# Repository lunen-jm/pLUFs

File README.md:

# pLUFs

The Physical LUFS meter will be a project that allows users to have realtime analysis of the LUFs level of the audio being transmitted by their PC.

The datasheets for the projects are located in the `datasheets` folder. Note that information surrounding the circular display can be found here: 

* Getting started: https://wiki.seeedstudio.com/get_start_round_display/
* Hardware: https://wiki.seeedstudio.com/seeedstudio_round_display_usage/

Information regarding the stepper gauge can be found here:

* https://www.adafruit.com/product/2424 

Information regarding stepper motor driver can be found here:

* https://www.adafruit.com/product/2448 
* https://learn.adafruit.com/adafruit-tb6612-h-bridge-dc-stepper-motor-driver-breakout/using-stepper-motors

The kiCad project for the PCB is located in the `pcbMain` folder. The PCB will be used in the display device, and will connect the Seeed XIAO ESP32C3 to the circular display, a Li-ION battery, and the gauge. It will also have a few tactile buttons.

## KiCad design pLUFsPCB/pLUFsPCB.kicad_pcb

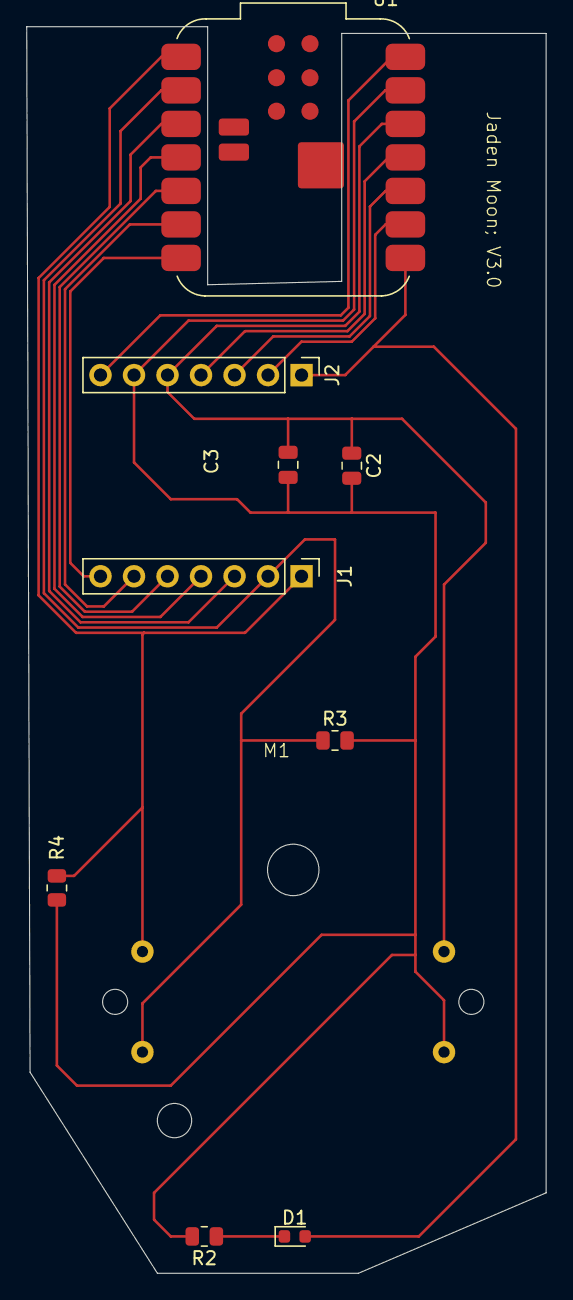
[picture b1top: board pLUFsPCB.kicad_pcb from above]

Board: 2 copper layers, 39.4 x 94.5 mm, 10 parts (0 on the bottom side), 14 nets.

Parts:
C2: 0.1μF; C_0805_2012Metric
C3: 10μF; C_0805_2012Metric
D1: LED; LED_0603_1608Metric
J1: Circular Display Pins (bottom); PinHeader_1x07_P2.54mm_Vertical
J2: Circular Display Pins (top); PinHeader_1x07_P2.54mm_Vertical
M1: Stepper_Motor_bipolar; x27_stepper
R2: R85; R_0805_2012Metric
R3, R4: 10kΩ; R_0805_2012Metric
U1: XIAO-ESP32-C3-SMD; MCU_Seeed_ESP32C3

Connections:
unnamed: D1.2 (A), J2.1, U1.3 (GPIO4_A2_D2)
unnamed: D1.1 (K), R2.1
unnamed: J1.1, M1.4, R4.2, U1.1 (GPIO2_A0_D0)
unnamed: J1.2, M1.3, R3.1, U1.2 (GPIO3_A1_D1)
unnamed: J1.4, U1.4 (GPIO5_A3_D3)
unnamed: J1.5, U1.5 (GPIO6_D4_SDA)
unnamed: J1.6, U1.6 (GPIO7_D5_SCL)
unnamed: J1.7, U1.7 (GPIO21_D6_TX)
unnamed: J2.2, U1.9 (GPIO8_D8_SCK)
unnamed: J2.3, U1.10 (GPIO9_D9_MISO)
unnamed: J2.4, U1.11 (GPIO10_D10_MOSI)
unnamed: C2.1, C3.1, J2.5, M1.1, U1.12 (3V3)
unnamed: C2.2, C3.2, J2.6, M1.2 (-), R2.2, R3.2, R4.1, U1.13 (GND)
unnamed: J2.7, U1.14 (5V)

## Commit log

2025-01-22 Initial Powerpoint slides for README
2025-01-22 Initial REAME upload
2025-01-22 pdf of README added
2025-01-29 KiCad Project Upload
    KiCad project added, initial README migrated, new README included
2025-03-11 lots
